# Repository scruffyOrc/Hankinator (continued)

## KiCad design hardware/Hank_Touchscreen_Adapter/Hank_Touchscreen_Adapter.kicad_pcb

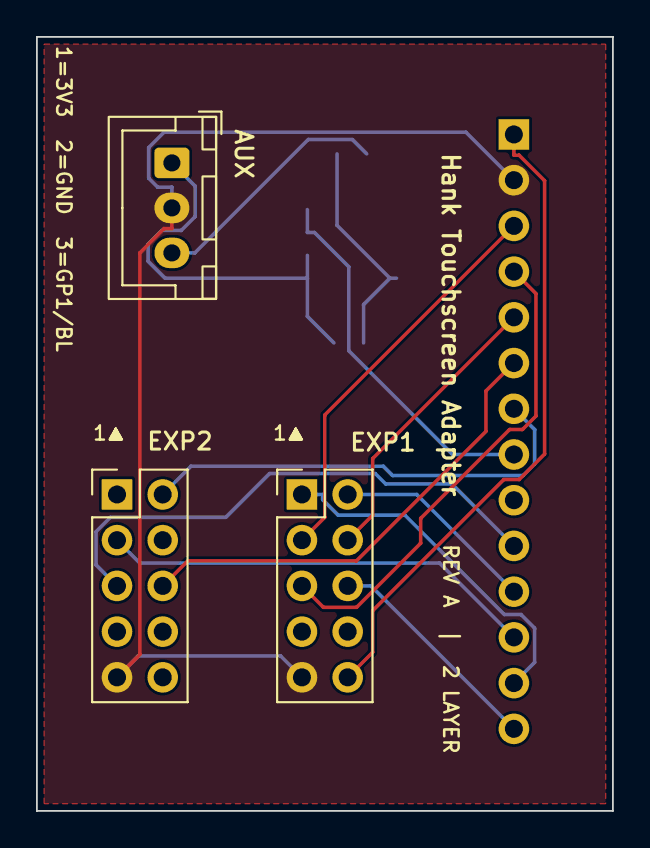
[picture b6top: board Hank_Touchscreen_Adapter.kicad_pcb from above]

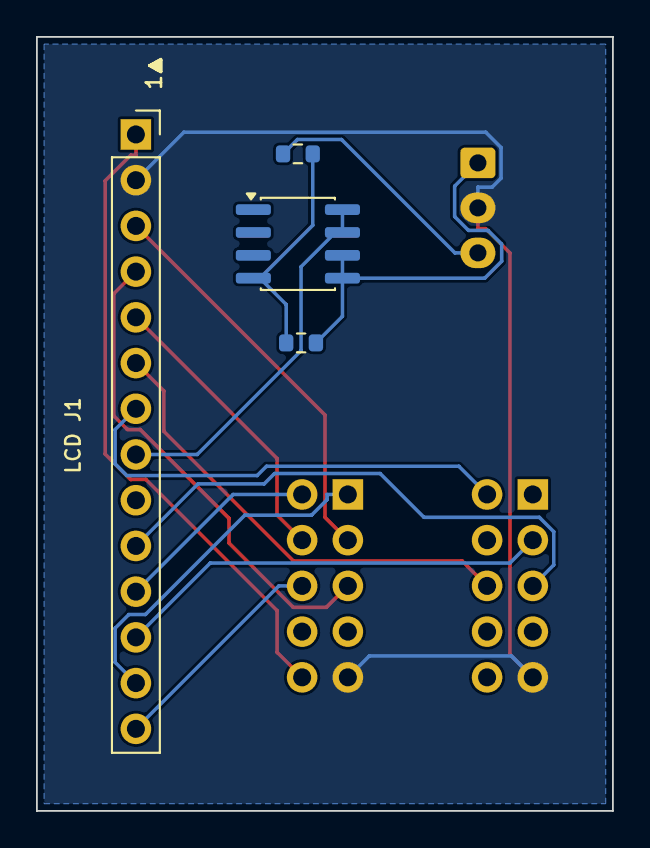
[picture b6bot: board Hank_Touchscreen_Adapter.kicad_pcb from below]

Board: 2 copper layers, 32.0 x 43.0 mm, 7 parts (4 on the bottom side), 16 nets.

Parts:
J1: LCD_ILI9488_XPT2046; PinSocket_1x14_P2.54mm_Vertical
J2: EXP1_TO_V1A; PinHeader_2x05_P2.54mm_Vertical
J3: EXP2_TO_V1A; PinHeader_2x05_P2.54mm_Vertical
J4: AUX_3V3_GND_GP1; JST_XH_B3B-XH-A_1x03_P2.50mm_Vertical
Q1: Si4599DY; SOIC-8_3.9x4.9mm_P1.27mm
R1: 1k; R_0603_1608Metric
R2: 100k; R_0603_1608Metric

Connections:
+3V3: J4.1, Q1.5, Q1.6, R2.2
+5V: J1.1, J2.10
BL_GATE: Q1.4, R1.2, R2.1
GND: J1.2, J2.9, J3.9, J4.2
GP1_BL_PWM: J4.3, R1.1
TFT_CS: J1.3, J2.3
TFT_DC: J1.5, J2.4
TFT_LED: J1.8, Q1.7, Q1.8
TFT_MOSI: J1.6, J3.6
TFT_RST: J1.4, J2.5
TFT_SCK: J1.7, J3.2
TOUCH_CLK: J1.10, J3.5
TOUCH_CS: J1.11, J2.2
TOUCH_DIN: J1.12, J3.3
TOUCH_DO: J1.13, J2.1
TOUCH_IRQ: J1.14, J2.6

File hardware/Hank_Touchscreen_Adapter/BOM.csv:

Reference,Qty,Value,Footprint,Notes
J1,1,LCD ILI9488/XPT2046,PinSocket_1x14_P2.54mm_Vertical,Female socket: mates with touchscreen's male 1x14 header
J2,1,EXP1 to V1A,PinHeader_2x05_P2.54mm_Vertical,Male: intended for female-to-female 10-conductor harness
J3,1,EXP2 to V1A,PinHeader_2x05_P2.54mm_Vertical,Male: intended for female-to-female 10-conductor harness
J4,1,AUX 3V3 GND GP1,JST-XH_B3B-XH-A_1x03_P2.50mm_Vertical,Pin 1 +3V3 pin 2 GND pin 3 GP1 BL PWM
Q1,1,Si4599DY,SOIC-8_3.9x4.9mm_P1.27mm,Use P-channel half only as 3V3 high-side LED PWM switch
R1,1,1k,R_0603_1608Metric,GP1 to Si4599 P-channel gate
R2,1,100k,R_0603_1608Metric,Gate-to-source reset pull-up

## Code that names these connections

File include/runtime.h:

#pragma once
#include <Arduino.h>
#include <U8g2lib.h>
#include "panel_pixels.h"
#include <EEPROM.h>
#include "pico/time.h"
#include "config.h"
#include "persistent_settings.h"

constexpr uint8_t LCD_CS=Pins::LcdCs,LCD_DC=Pins::LcdDc,LCD_RESET=Pins::LcdReset,LCD_CLOCK=Pins::LcdClock,LCD_DATA=Pins::LcdData;
constexpr uint8_t ENC_CLICK=Pins::EncoderClick,ENC_A=Pins::EncoderA,ENC_B=Pins::EncoderB,BEEPER=Pins::Beeper,NEOPIXEL_PIN=Pins::NeoPixel,STOP_BUTTON=Pins::Stop;
constexpr uint8_t STEPPER_STEP=Pins::Step,STEPPER_DIR=Pins::Dir,STEPPER_ENABLE=Pins::Enable,HEARTBEAT_LED=Pins::Heartbeat;
constexpr bool WIND_DIRECTION_HIGH=Config::WindDirectionHigh;
constexpr uint8_t NEOPIXEL_COUNT=3;

namespace Config {
constexpr uint32_t STEPS_PER_MOTOR_REV=StepsPerMotorRev,STEPS_PER_HUB_REV=StepsPerHubRev;
constexpr float LAUNCH_MOTOR_RPS=LaunchMotorRps,LAUNCH_RAMP_TURNS=LaunchRampTurns;
constexpr float START_MOTOR_RPS=StartMotorRps,CRUISE_MOTOR_RPS=CruiseMotorRps,END_MOTOR_RPS=EndMotorRps;
constexpr uint32_t START_HOLD_MS=StartHoldMs,ACCEL_RAMP_MS=AccelRampMs;
constexpr float DECEL_TURNS=DecelTurns,PAUSE_END_MOTOR_RPS=PauseEndMotorRps,PAUSE_RAMP_TURNS=PauseRampTurns;
constexpr float RESUME_START_MOTOR_RPS=ResumeStartMotorRps;
constexpr int SPEED_TRIM_MIN_PERCENT=SpeedTrimMin,SPEED_TRIM_MAX_PERCENT=SpeedTrimMax,SPEED_TRIM_STEP_PERCENT=SpeedTrimStep;
constexpr int MIN_TURNS=MinTurns,MAX_TURNS=MaxTurns;
constexpr uint32_t STEP_PULSE_US=StepPulseUs,IDLE_TIMER_US=IdleTimerUs,SPLASH_TIME_MS=SplashTimeMs,RAINBOW_CYCLE_MS=RainbowCycleMs;
constexpr size_t EEPROM_SIZE=EepromSize;
constexpr uint32_t SETTINGS_MAGIC=SettingsMagic;
constexpr uint16_t SETTINGS_VERSION=SettingsVersion;
}

struct YarnWeight{const char* label;};
struct SkeinSize{const char* label;uint16_t factoryDefaultTurns;};
inline constexpr YarnWeight YARN_WEIGHTS[]={{"Lace/Suri"},{"Fingering"},{"Sport"},{"DK"},{"Worsted"},{"Chunky"},{"Bulky"},{"Jumbo"}};
inline constexpr SkeinSize SKEIN_SIZES[]={{"Mini",63},{"Half",90},{"Full",110}};
inline constexpr int YARN_WEIGHT_COUNT=sizeof(YARN_WEIGHTS)/sizeof(YARN_WEIGHTS[0]);
inline constexpr int SKEIN_SIZE_COUNT=sizeof(SKEIN_SIZES)/sizeof(SKEIN_SIZES[0]);
static_assert(YARN_WEIGHT_COUNT==SettingsLayout::YarnCount&&SKEIN_SIZE_COUNT==SettingsLayout::SizeCount,"EEPROM matrix dimensions must remain compatible");
enum class ProductMode:uint8_t{Turninator,Fuhgeddabouditinator,LoadCellFault};
enum class FuhProgram:uint8_t{Mini,Half,Full};
enum class UiState{AUTO_MODE_SELECT,TURN_SELECT,FUH_PROGRAM_SELECT,TARING,TARE_FAILED,LOAD_YARN,WINDING,COMPLETE,REPEAT_PROMPT,CONFIG_MENU,CONFIG_CONNECTIVITY_MENU,CONFIG_MACHINE_SETTINGS_MENU,CONFIG_DIAGNOSTICS_MENU,CONFIG_MOTOR_MENU,CONFIG_RUN_CURRENT,CONFIG_HOLD_CURRENT,CONFIG_DIRECTION,CONFIG_RECOVERY_LIMIT,CONFIG_WEIGHT_MENU,CONFIG_WEIGHT_VALUE,CONFIG_PAIRING,CONFIG_LOAD_CELL_DIAGNOSTICS,CONFIG_FIRMWARE_UPDATE,LOAD_CELL_FAULT,HALL_SEEK,HALL_FAILED,CONFIG_WEIGHT_DIAGNOSTICS,CONFIG_LOAD_CELL_TIMING,CONFIG_COMMISSIONING,SCALE_MODE,HAND_TURNING};
enum class PauseState:uint8_t{RUNNING,RAMPING_DOWN,PAUSED,RAMPING_UP};
enum class MotionPhase:uint8_t{LAUNCH,START_HOLD,ACCEL,CRUISE,DECEL,PAUSE_DOWN,PAUSED,RESUME};

extern U8G2_UC1701_MINI12864_F_4W_SW_SPI display;
extern PanelPixels pixels;
extern PersistentSettings settings;
extern ProductMode productMode;
extern bool weightCapabilityEnabled;
extern uint8_t detectedLoadCellCount;
extern UiState uiState;
extern volatile PauseState pauseState;
extern volatile uint32_t pauseRampStartStep,pauseRampStopStep;
extern float pauseRampStartRPS;
extern uint32_t pauseStartedTime,totalPausedTime,resumeRampStartedTime;
extern bool pauseTimeRecorded;
extern int selectedYarnWeight,selectedSkeinSize,selectedTurns;
extern int selectedCruiseSpeedIndex;
extern float selectedCruiseMotorRPS;
extern FuhProgram selectedFuhProgram,activeFuhProgram;
extern bool repeatYes;
extern bool autoCountMode;
extern int speedTrimPercent;
extern float currentMotorRPS;
extern uint32_t windingStartTime;
extern uint32_t finalRunStepCount;
extern float finalRunWeightGrams;
extern bool finalRunWeightValid;
extern bool finalRunAborted;
extern uint32_t launchCompleteElapsedMs;
extern volatile bool motionActive;
extern volatile uint32_t currentStepCount,targetStepCount,requestedStepRateHz;
extern volatile uint32_t motionSegmentStopStep;
extern alarm_id_t stepAlarmId;
extern int lastA;
extern bool lastClick,lastStop,heartbeatState;
extern uint32_t lastTurnEncoderTime,lastHeartbeat;
extern int configMenuSelection;
extern int configSubMenuSelection;
extern int motorMenuSelection;
extern int weightTargetMenuSelection;
